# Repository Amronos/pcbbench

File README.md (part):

# PCBBench

> [!NOTE]
> PCBBench is still under development.

PCBBench compares AI models and agents on PCB design performance across 40+ metrics.

See every board, score and review at [pcbbench-five.vercel.app](https://pcbbench-five.vercel.app).

## The task

The prompt is [bench/prompt.md](bench/prompt.md).

## Results

### Complete scores

| Run                                                            | Design review (20) | Circuit checks (20) | Layout checks (30) | Orderable (20) | Parts data (10) | Failed gate | Score (100) | 5 boards, per board | AI cost |
| -------------------------------------------------------------- | ------------------ | ------------------- | ------------------ | -------------- | --------------- | ----------- | ----------- | ------------------- | ------- |
| [`sprocket--opus-5.5`][sprocket]                               | 9                  | 18.2                | 24.1               | 20             | 9.9             |             | **81.2**    | $73.36              | $53.31  |
| [`sprocket--gpt-6.1-sol`][sprocket]                            | 8                  | 19.3                | 19                 | 20             | 5               |             | **71.3**    | $148.08             | $53.72  |
| [`backplane--opus-5.5`][backplane]                             | 17                 | 17.8                | 15.4               | 10             | 9.8             |             | **69.9**    | $51.57              | $56.77  |
| [`backplane--fable-5.2`][backplane]                            | 16                 | 16.5                | 14                 | 15             | 7               |             | **68.4**    | $52.68              | $49.09  |
| [`codex-desktop`][codex][`-texttocad--gpt-6.1-sol`][texttocad] | 11                 | 20                  | 16.7               | 4              | 4.7             |             | **56.4**    | $87.53              | $14.36  |
| [`backplane--gpt-6.1-sol`][backplane]                          | 9                  | 9.2                 | 14.5               | 12             | 4.8             | −20         | **29.5**    | $181.34             | $5.81   |
| [`codex-desktop--gpt-6.1-sol`][codex]                          | 7                  | 15.6                | 9.2                | 14             | 0               | −20         | **25.9**    | $77.64              | $6.41   |

The score covers the board only. Price, AI cost and time are left out of it, so they can be weighed separately. Each item earns its points times a fraction from 0 to 1:

| Group          | Item                  | Points | Fraction                                                                                                    |
| -------------- | --------------------- | ------ | ----------------------------------------------------------------------------------------------------------- |
| Design review  | Layout                | 10     | 1 minus 0.1 per minor and 0.2 per major layout finding, down to 0                                           |
|                | Routing               | 10     | the same, for routing findings                                                                              |
| Circuit checks | Decoupling            | 5      | RP2350 power pins with a capacitor within 3.2 mm                                                            |
|                | USB protection        | 5      | 0.5 for an ESD part on D+ and D-, plus 0.25 for each line with a series resistor                            |
|                | Antenna keepout       | 5      | 1 when there are keepouts and no copper is in them                                                          |
|                | Battery drain         | 5      | 1 at 5 µA or less drawn by unswitched battery dividers, falling linearly to 0 at 25 µA                      |
| Layout checks  | Thermal pads          | 10     | mean over the exposed pads of their vias over the number needed, 0 for a pad with no plane on another layer |
|                | Grounding             | 10     | USB, QSPI and microSD track length over a ground plane on the next layer                                    |
|                | Silkscreen            | 5      | texts at least 0.8 mm high                                                                                  |
|                | Board size            | 5      | 1 at the Feather RP2350's 50.8 × 22.8 mm area or less, falling linearly to 0 at 5 times that area           |
| Orderable      | Fab notes             | 5      | 1 when every fab option in the notes can be ordered from PCBWay                                             |
|                | Board                 | 5      | 1 when the board needs no rework                                                                            |
|                | BOM lines             | 10     | 1 minus 0.2 for each BOM line that needs a fix, down to 0                                                   |
| Parts data     | 3D models             | 5      | parts with a 3D model                                                                                       |
|                | Supplier part numbers | 5      | BOM lines with a valid number from at least one supplier                                                    |

A board that fails a gate loses 20 points. The gates are a missing prompt feature, a failed crystal, button or power-path check, and a fatal review finding. Two boards fail one, each from a fatal finding listed under [Design review](#design-review). The group columns leave out the penalty. `bench/score.ts` computes the score and writes it under `score` in `metrics.json`. Differences under about 5 points aren't meaningful. Moving 10 points between any two groups moves runs by up to 2 places, and `sprocket--opus-5.5` stays first every time. `backplane--opus-5.5` and `backplane--fable-5.2`, 1.5 points apart, swap places in most shifts.

### Time, cost and price

| Run                                                            | Minutes | AI cost | Tokens, incl. cache reads | Board size (mm) | 1 board | 5 boards, per board | Prices after fixes |
| -------------------------------------------------------------- | ------- | ------- | ------------------------- | --------------- | ------- | ------------------- | ------------------ |
| [`codex-desktop--gpt-6.1-sol`][codex]                          | 78.1    | $6.41   | 21.0M                     | 80 × 65         | $246.31 | $77.64              | yes                |
| [`codex-desktop`][codex][`-texttocad--gpt-6.1-sol`][texttocad] | 96.0    | $14.36  | 52.4M                     | 80 × 75         | $297.32 | $87.53              | yes                |
| [`backplane--opus-5.5`][backplane]                             | 170.5   | $56.77  | 124.9M                    | 80 × 38         | $185.16 | $51.57              | yes                |
| [`backplane--gpt-6.1-sol`][backplane]                          | 98.2    | $5.81   | 28.6M                     | 85 × 70         | $741.00 | $181.34             | yes                |
| [`backplane--fable-5.2`][backplane]                            | 225.4   | $49.09  | 55.6M                     | 76.2 × 22.86    | $187.53 | $52.68              | yes                |
| [`sprocket--opus-5.5`][sprocket]                               | 291.0   | $53.31  | 90.1M                     | 28 × 78.54      | $282.37 | $73.36              | no                 |
| [`sprocket--gpt-6.1-sol`][sprocket]                            | 95.8    | $53.72  | 185.1M                    | 85 × 65         | $659.08 | $148.08             | no                 |

- **Minutes:** the time the agent was working.
- **AI cost:** the run's API cost at market prices, including subagents.
- **Board price:** PCB, assembly and parts, at PCBWay's normal instant-quote prices, without shipping or the new-customer $29 promo. PCBWay makes at least 5 bare PCBs, so "1 board" means 5 PCBs with 1 assembled. "5 boards" is 5 PCBs, all assembled. Parts are priced at distributor list prices for the larger of the quantity needed and the minimum order.
- **Prices after fixes:** The design couldn't be ordered exactly as delivered, so the price covers the changes listed under `fixes` in `metrics.json`. Examples are invalid or legacy part numbers, or a fab option PCBWay doesn't offer.

### BOM and 3D models

| Run                                                            | Missing 3D models | BOM lines | BOM lines fixed | Valid LCSC part numbers | Valid Digi-Key part numbers | Mouser part numbers |
| -------------------------------------------------------------- | ----------------- | --------- | --------------- | ----------------------- | --------------------------- | ------------------- |
| [`codex-desktop--gpt-6.1-sol`][codex]                          | 121               | 51        | 1               | 0%                      | 0%                          | 0%                  |
| [`codex-desktop`][codex][`-texttocad--gpt-6.1-sol`][texttocad] | 7                 | 53        | 2               | 0%                      | 0%                          | 0%                  |
| [`backplane--opus-5.5`][backplane]                             | 4                 | 38        | 0               | 100%                    | 0%                          | 0%                  |
| [`backplane--gpt-6.1-sol`][backplane]                          | 5                 | 54        | 1               | 0%                      | 0%                          | 0%                  |
| [`backplane--fable-5.2`][backplane]                            | 7                 | 36        | 0               | 50%                     | 0%                          | 0%                  |
| [`sprocket--opus-5.5`][sprocket]                               | 1                 | 40        | 0               | 100%                    | 0%                          | 0%                  |
| [`sprocket--gpt-6.1-sol`][sprocket]                            | 0                 | 55        | 0               | 0%                      | 0%                          | 0%                  |

- **Parts:** footprints on the board that aren't marked board-only, excluded from the BOM or DNP, and aren't bare test pads.
- **Missing 3D models:** parts with no 3D model, or with one that the run's own KiCad version can't load from its stock libraries and the project's files.
- **Supplier part numbers:** the share of BOM lines that give a valid part number for that supplier. An LCSC number is valid when LCSC lists it under the line's manufacturer part number. A Digi-Key number is valid when Digi-Key lists it as a variation of that part. Mouser numbers can't be looked up, so any Mouser number counts. `suppliers` in `metrics.json` has the counts.
- Every BOM covers every part. No BOM listed a designator that isn't on the board, had a Qty that doesn't match its designators, or left out a manufacturer part number for a fitted part.
- `backplane--fable-5.2` excludes its pin headers from the BOM and `sprocket--opus-5.5` marks its pin headers do not populate, so PCBWay wouldn't fit them. They aren't counted as parts. The judge sees this.

### Design and fab checks

| Run                                                            | DRC errors | DRC warnings | ERC errors | ERC warnings | BOM lines LCSC, JLCPCB or Digi-Key stocks for 5 boards | Lines discontinued at LCSC or Digi-Key |
| -------------------------------------------------------------- | ---------- | ------------ | ---------- | ------------ | ------------------------------------------------------ | -------------------------------------- |
| [`codex-desktop--gpt-6.1-sol`][codex]                          | 0          | 0            | 0          | 0            | 94.1%                                                  | 3                                      |
| [`codex-desktop`][codex][`-texttocad--gpt-6.1-sol`][texttocad] | 0          | 0            | 0          | 0            | 98.1%                                                  | 6                                      |
| [`backplane--opus-5.5`][backplane]                             | 3          | 0            | 0          | 0            | 100%                                                   | 0                                      |
| [`backplane--gpt-6.1-sol`][backplane]                          | 0          | 2            | 0          | 0            | 92.6%                                                  | 5                                      |
| [`backplane--fable-5.2`][backplane]                            | 0          | 1            | 0          | 0            | 100%                                                   | 0                                      |
| [`sprocket--opus-5.5`][sprocket]                               | 0          | 0            | 0          | 0            | 100%                                                   | 1                                      |
| [`sprocket--gpt-6.1-sol`][sprocket]                            | 0          | 0            | 0          | 0            | 100%                                                   | 7                                      |

- **DRC:** run with zones refilled, because some boards were saved with stale fills. It includes the schematic parity check. No board had unconnected items or parity issues. Copper narrower than the board's minimum connection width (`connection_width`) counts as an error, though KiCad only warns. The only cases are on `backplane--opus-5.5`, where inner-layer copper necks down to 0.079 mm, below the 5 mil (0.127 mm) minimum its PCBWay quote orders. Footprints that differ from their library copy (`lib_footprint_mismatch`) aren't counted. `metrics.json` has the counts by type.
- **Stock:** a line counts as stocked when LCSC, JLCPCB or Digi-Key has its quantity × 5 on hand, because PCBWay buys from many distributors. JLCPCB is searched by LCSC number when the line has one, else by manufacturer part number. Digi-Key is searched by manufacturer part number, including packaging variants such as `/TR`. Every run's stock was checked on the same day.
- **Discontinued:** LCSC lists the part as discontinued, or every Digi-Key listing of it is Obsolete or Discontinued at Digi-Key. Some of these parts are still in stock.
- **Fab files:** every Gerber and drill file in the order zip matches a fresh export from the board, layer by layer, within 0.1% of the drawn area. Every zip has all copper layers, Edge.Cuts, both masks, F.Silkscreen, paste for each side with surface-mount parts, and the drill files.
- **Placement:** every placement file lists every surface-mount part once, on the right side and at the board's rotation. After lining up the file's origin and axes with the board, every part is within 0.5 mm of its board position.
- **Footprints:** each part's pad count matches LCSC's footprint for its part number. Connectors aren't compared, because libraries split shield tabs and doubled contacts differently.
- **Prompt features:** every BOM has a part for the RP2350, QSPI flash, PSRAM, USB-C, Wi-Fi and BLE, microSD, Qwiic, an RGB LED and a power-path charger. Every board monitors the battery, with a fuel gauge or a resistor from a battery net to an ADC pin, directly or through a transistor.
- **Deliverables:** every run has a README, a schematic and project file next to the board, and a fab folder.
- The files checked are `board`, `bom`, `placement` and `fabZip` in `info.json`. `metrics.json` lists the designators and per-layer results.

### Circuit checks

| Run                                                            | RP2350 power pins with a capacitor within 3.2 mm | Pins farther away (mm)                                                                    | Battery divider                     | Divider current at 4.2 V (µA) | Divider switched | Antenna keepouts    | Copper in the keepouts |
| -------------------------------------------------------------- | ------------------------------------------------ | ----------------------------------------------------------------------------------------- | ----------------------------------- | ----------------------------- | ---------------- | ------------------- | ---------------------- |
| [`codex-desktop--gpt-6.1-sol`][codex]                          | 13 of 14                                         | QSPI_IOVDD 54: 3.43                                                                       | R25 100k / R26 100k, buffered by U8 | 21                            | no               | U9 footprint        | none                   |
| [`codex-desktop`][codex][`-texttocad--gpt-6.1-sol`][texttocad] | 14 of 14                                         | none                                                                                      | R10 470k / R11 470k, buffered by U9 | 4.47                          | no               | U6 footprint        | none                   |
| [`backplane--opus-5.5`][backplane]                             | 14 of 14                                         | none                                                                                      | R9 200k / R10 100k                  | 14                            | no               | U7 footprint, board | none                   |
| [`backplane--gpt-6.1-sol`][backplane]                          | 9 of 14                                          | DVDD 6: 3.45, IOVDD 11: 3.66, DVDD 23: 3.59, DVDD 39: 6.4, ADC_AVDD 44: 12.15             | R25 100k / R26 100k                 | 21                            | no               | U8 footprint, board | /3V3 fill on In4.Cu    |
| [`backplane--fable-5.2`][backplane]                            | 8 of 14                                          | IOVDD 1: 3.34, DVDD 6: 7.34, IOVDD 11: 3.69, IOVDD 20: 4.27, DVDD 23: 6.05, DVDD 39: 4.08 | R12 200k / R13 200k                 | 10.5                          | no               | board               | none                   |
| [`sprocket--opus-5.5`][sprocket]                               | 9 of 14                                          | DVDD 6: 4.53, IOVDD 11: 4.53, IOVDD 20: 7.05, DVDD 23: 6.17, IOVDD 30: 6.43               | R14 470k / R15 470k                 | 4.47                          | no               | U7 footprint        | none                   |
| [`sprocket--gpt-6.1-sol`][sprocket]                            | 12 of 14                                         | DVDD 6: 3.3, IOVDD 11: 3.3                                                                | R23 100k / R24 100k                 | 21                            | yes              | U6 footprint        | none                   |

| Run                                                            | D+ length (mm) | D- length (mm) | Mismatch (mm) | Vias | Width (mm) | Gap (mm) | Side by side (mm) | Differential impedance (Ω) | ESD parts on D+ and D- |
| -------------------------------------------------------------- | -------------- | -------------- | ------------- | ---- | ---------- | -------- | ----------------- | -------------------------- | ---------------------- |
| [`codex-desktop--gpt-6.1-sol`][codex]                          | 51.45          | 52.84          | 1.39          | 2    | 0.15       | 0.15     | 37.66             | 87.9                       | U5                     |
| [`codex-desktop`][codex][`-texttocad--gpt-6.1-sol`][texttocad] | 28.51          | 24.53          | 3.98          | 4    | 0.15       | 0.15     | 8.29              | 95.5                       | U8                     |
| [`backplane--opus-5.5`][backplane]                             | 38.02          | 38.29          | 0.27          | 0    | 0.25       | 1.25     | 11.78             | 120.9                      | U1                     |
| [`backplane--gpt-6.1-sol`][backplane]                          | 58.54          | 42.65          | 15.89         | 6    | 0.22       | 1.68     | 9.93              | no stackup                 | U5                     |
| [`backplane--fable-5.2`][backplane]                            | 44.52          | 42.26          | 2.26          | 3    | 0.15       | 0.16     | 4.86              | 114.7                      | U6                     |
| [`sprocket--opus-5.5`][sprocket]                               | 66.19          | 50.77          | 15.42         | 0    | 0.2        | 0.15     | 32.9              | 100.3                      | U4                     |
| [`sprocket--gpt-6.1-sol`][sprocket]                            | 23.84          | 25.79          | 1.95          | 2    | 0.22       | 0.15     | 8.76              | 90.7                       | D1                     |

- **Decoupling:** for each RP2350 IOVDD, DVDD, QSPI_IOVDD, USB_OTP_VDD, ADC_AVDD, VREG_VIN and VREG_AVDD pad, the nearest capacitor with one pad on that pin's net and the other on a ground net, on either side of the board. The distance is from the center of the pin's pad to the center of the capacitor's nearest pad. Pins are found by the pads' pin functions, or by RP2350A pad numbers when the footprint names none. Hardware design with RP2350 asks for decoupling close to the power pins without giving a distance. Its own Minimal board, whose capacitors it calls slightly further from the chip than optimal, has one within 3.2 mm of every power pin.
- **Battery divider:** the resistor from the battery to the ADC input, or to the op-amp follower that drives it, and the resistor from there to ground. The current is 4.2 V over their sum, from the footprint values. A divider is switched when its top resistor reaches the battery through a transistor or load switch rather than directly.
- **USB:** D+ and D- run from the RP2350 pins through the series resistors to the USB-C connector. Lengths add every track segment and arc on those nets, including stubs. Width and gap are for the longest stretch where D+ and D- segments run parallel on one layer within 2 mm of each other, and "side by side" is that stretch's length. The impedance uses the IPC-2141 edge-coupled microstrip formula with that width and gap and the board's stackup. `backplane--gpt-6.1-sol` has no stackup in its board file.
- **ESD parts:** parts other than the connector and the RP2350 with pads on both D+ and D-.
- **USB impedance isn't scored.** The RP2350 only does USB full speed. Its edges take 4 ns or more, so traces a few centimeters long behave as plain wires, and 90 Ω matching doesn't change how the link works. The same goes for how close the series resistors sit to the RP2350, which is why USB protection only checks that the ESD part and resistors are there.
- **Battery drain:** a LiPo board draws this current all the time, even when off, unless the divider is switched. `sprocket--gpt-6.1-sol` switches its divider with Q1, so it scores full points. The op-amp followers on `codex-desktop--gpt-6.1-sol` and `codex-desktop-texttocad--gpt-6.1-sol` aren't counted.
- **Antenna keepouts:** rule areas in the Wi-Fi module's footprint or on the board that overlap the module's courtyard and forbid copper. Copper in them counts tracks, vias, zone fills and other parts' pads on every copper layer, including layers the rule area doesn't cover. The rule area in the `backplane--fable-5.2` module footprint lies off the board, so only its board rule area counts.
- `design` in `metrics.json` has the per-pin distances, resistor values, net names and keepout layers.

### Layout checks

| Run                                                            | Exposed pad vias, of those needed | Thermal points | Grounded USB / QSPI / microSD | Grounding points | Texts at least 0.8 mm | Silkscreen points | Board area (mm²) | Board size points |
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
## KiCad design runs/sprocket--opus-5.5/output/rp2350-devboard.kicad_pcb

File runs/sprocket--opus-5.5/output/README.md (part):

# RP2350 dev board

A 28 × 78.54 mm, 4-layer RP2350A board with Wi-Fi/BLE, a LiPo charger and microSD, laid out for PCBWay's
standard PCB and turnkey assembly service. Every fitted part is on the top side.

| Block | Part | Notes |
| --- | --- | --- |
| MCU | RP2350A (U1), 12 MHz crystal | Core supply from the internal switching regulator (L1 3.3 µH) |
| Flash | W25Q128JVSIQ (U2), 16 MB | QSPI CS0, boots from it |
| PSRAM | APS6404L-3SQR-SN (U3), 8 MB | QSPI CS1 on GPIO8 |
| USB | USB-C (J1, GCT USB4105), 5.1 kΩ CC pull-downs, USBLC6-2 ESD | USB 2.0 full speed, power and data |
| Charger | BQ24074 (U5) with power path | 445 mA charge current, 500 mA input limit |
| Battery | JST PH 2-pin (J2), reverse-polarity P-FET (Q1) | Single-cell LiPo |
| Battery monitor | 470 k/470 k divider on GPIO28 (ADC2), switched by Q2 | `VBAT = 2 × ADC` |
| 3.3 V | TPS63001 buck-boost (U6) | Runs from the cell or USB; 3V3_EN on the header turns it off |
| Wireless | Raspberry Pi RM2 module (U7, CYW43439) | Wi-Fi 4 and Bluetooth 5.2, same wiring as the Pico 2 W |
| microSD | Molex 104031-0811 (J3) | 4-bit SD on GPIO10-15, card detect on GPIO9 |
| Qwiic / STEMMA QT | JST SH 4-pin (J4) | I²C0 on GPIO4 (SDA) and GPIO5 (SCL), 2.2 kΩ pull-ups |
| RGB LED | WS2812B-2020 (D3) | Data on GPIO22 |
| Buttons | BOOTSEL (SW1), RESET (SW2) | |
| Headers | 2 × 14 pins on 2.54 mm, rows 22.86 mm apart (J5, J6) | Holes only; not fitted. Pin names on the bottom silkscreen |

## Files

| Path | Contents |
| --- | --- |
| `rp2350-devboard.kicad_pro` | KiCad project: schematic (5 sheets) and PCB |
| `BOM.csv` | Bill of materials |
| `fab/` | Gerbers, drill files and job file (`gerbers/`, zipped as `rp2350-devboard-gerbers.zip`), PCBWay BOM and centroid |
| `docs/assembly.md` | Assembly and bring-up instructions |
| `docs/renders/` | 3D renders |
| `lib/` | Project symbols, footprints and 3D models |
| `scripts/` | Generators: `design.py` holds every part and net, the other scripts build the schematic and board, finish it (`teardrops.py`, `label_board.py`) and export `fab/` (`export_fab.py`) |

The schematic, placement and pre-routed copper come from the scripts. Edit the schematic and board in KiCad now.
`build_schematic.py` assigns new UUIDs, which breaks the link to the routed board, and `build_pcb.py` replaces the
routed board.

## Pinout

Left header J5, pin 1 at the top (USB-C is at the bottom):

| Pin | 1 | 2 | 3 | 4 | 5 | 6 | 7 | 8 | 9 | 10 | 11 | 12 | 13 | 14 |
| --- | --- | --- | --- | --- | --- | --- | --- | --- | --- | --- | --- | --- | --- | --- |
| J5 | GND | 3V3 | SWCLK | SWDIO | RUN | GP16 | GP17 | GP18 | GP19 | GP20 | GP21 | GP26/A0 | GP27/A1 | GND |
| J6 | GND | VBUS | GND | 3V3 | GP7 | GP6 | GP5/SCL | GP4/SDA | GP3 | GP2 | GP1 | GP0 | GND | 3V3_EN |

Fixed functions:

| GPIO | Function |
| --- | --- |
| 8 | PSRAM CS |
| 9 | microSD card detect (low when a card is in) |
| 10-15 | microSD CLK, CMD, D0, D1, D2, D3 |
| 22 | WS2812B data |
| 23, 24, 25, 29 | RM2 WL_ON, WL_D, WL_CS, WL_CLK (as on the Pico 2 W) |
| 28 | Battery voltage / 2 |

## Design decisions

- **Pico 2 W compatible wireless.** The RM2 uses GPIO23/24/25/29 and the same 470 Ω/10 kΩ data network, and its
  WL_GPIO2 senses VBUS through a 100 k/150 k divider. Stock MicroPython and the Pico SDK `pico2_w` board files
  drive Wi-Fi and BLE unchanged.
- **No WL_GPIO0 LED.** The Pico 2 W's LED hangs off the RM2. Its track would block the left header fan-out, and the
  RGB LED already serves as the user LED, so U7 pin 8 is unconnected. `Pin("LED")` on stock `pico2_w` firmware
  runs without error but lights nothing. Use the WS2812B on GPIO22.
- **Charger in USB500 mode.** EN1 is tied high and EN2 low, so the BQ24074 draws at most 500 mA from any USB port
  without negotiation. ISET = 2 kΩ sets 445 mA fast charge, which suits cells from about 450 mAh up. R10 (ILIM) only
  matters if EN1/EN2 are changed to resistor-programmed mode.
- **Power path.** The BQ24074 OUT pin (VSYS) feeds the TPS63001 from USB when present, else from the cell. The
  buck-boost keeps 3.3 V across the full LiPo range (3.0-4.2 V) and from USB (VSYS = 4.4 V).
- **VSYS not on the header.** VSYS is tied to the cell through the charger's internal BAT-OUT FET, so 5 V fed there
  would charge the cell with no regulation. External 5 V power goes in through VBUS (J6 pin 2), which passes the
  charger's input current limit and over-voltage protection.
- **3V3_EN.** Pulled up to VSYS with 100 kΩ. Grounding J6 pin 14 turns off 3.3 V while the charger keeps working.
- **Battery monitor back-power blocker.** The divider reads VBAT/2, up to 2.1 V. With the 3.3 V rail off, that
  voltage would forward-bias the GPIO28 clamp diode into an unpowered IOVDD. Q2, an N-FET gated by +3V3, connects
  the divider to the pin only while 3.3 V is up. The divider draws 4.5 µA from the cell.
- **2.2 kΩ PSRAM CS pull-up.** At power-on the RP2350 pulls GPIO8 down (36 kΩ minimum). 2.2 kΩ keeps CE# above
  the PSRAM's V_IH so it stays deselected until firmware configures CS1.
- **Reverse-battery P-FET (Q1).** A reversed cell leaves the FET off, so the charger and buck-boost see no
  negative voltage.
- **Headers not fitted.** J5/J6 are holes only, so the board can be soldered down, socketed or fitted with headers
  by the user. J1's four shell tabs are the only plated through-holes that get solder. PCBWay solders them with
  paste-in-hole or by hand.

## Layout

- Stackup: PCBWay standard 1.6 mm 4-layer, 1 oz outer copper, ENIG. F.Cu signals and parts, In1.Cu solid GND
  with no tracks, In2.Cu +3.3 V plane that also carries signals (see the reviewer notes), B.Cu signals with GND
  pour.
- Rules: 0.15 mm track and clearance for signals (PCBWay minimum 0.127 mm), 0.6/0.3 mm vias, USB pair 0.2 mm.
- Power copper: VBUS, VSYS, VBAT, BAT_CONN and the inductor nets run at 0.4 mm and +1V1 at 0.2-0.25 mm. The
  narrowest pieces are 0.15 mm stubs where they enter fine-pitch pins: about 0.7 mm of VBAT at U5's BAT pins and
  the EN1 tie to VSYS. +3V3 reaches the parts through the In2 plane.
- The RM2 sits at the top edge with its antenna past the copper. Its footprint carries the datasheet's RF keepout on
  all copper layers. The datasheet forbids metal only in the antenna keepout, so tracks and vias run under the module
  body.
- The RP2350 regulator follows Raspberry Pi's hardware design guide: VREG_LX runs between the C12 and C13 pads to
  L1. A custom DRC rule allows that one net 0.127 mm clearance, still at PCBWay's minimum.
- Switch-node keepouts on In2.Cu and B.Cu keep signal tracks out of the fields under the buck-boost (tracks and
  vias) and the RP2350 regulator (tracks only, so a GND via can drop the C12/C13 return straight to the plane).
  GND still pours in both.
- Drawn by hand in `scripts/hand_routes.py` and `scripts/build_pcb.py`: the top-left fan-out (SWD, RUN, GP16-27,
  VBAT_SENSE, RGB_DIN and the RM2 lines), USB_D±_MCU from U1 to R3/R4, the VREG_LX loop, and the buck-boost
  BB_L1/BB_L2/VSYS/+3V3 loop. The USB pair was routed as a differential pair and locked before the autoroute.
  The router did the rest, then GND stitching vias and a 3 mm edge fence went in.
- Teardrops on every pad and via. Reference designators are hidden on the silkscreen and shown on F.Fab.

## Reviewer notes

- **DRC.** ERC is clean. DRC has 0 errors, 0 unconnected items and clean schematic parity. One warning remains:
  R7's top silk line touched U3's pin-1 mark and was deleted, so R7 no longer matches its library footprint.
- **Via in pad.** The router put 82 vias in or against SMD pads, such as on the decoupling caps, U1, U2, U3 and J1.
  They are marked filled and capped, so the order needs PCBWay's resin-filled, capped vias, which cost more. Moving
  them beside the pads by hand would allow plain tented vias.
- **In2 is a split plane.** About 410 mm of other nets run on In2.Cu: SD bus, RUN, GP4, QSPI_SCLK (23 mm),
  PSRAM_CS, +1V1, VBUS and others. The +3.3 V copper still connects everywhere, but these traces reference a
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
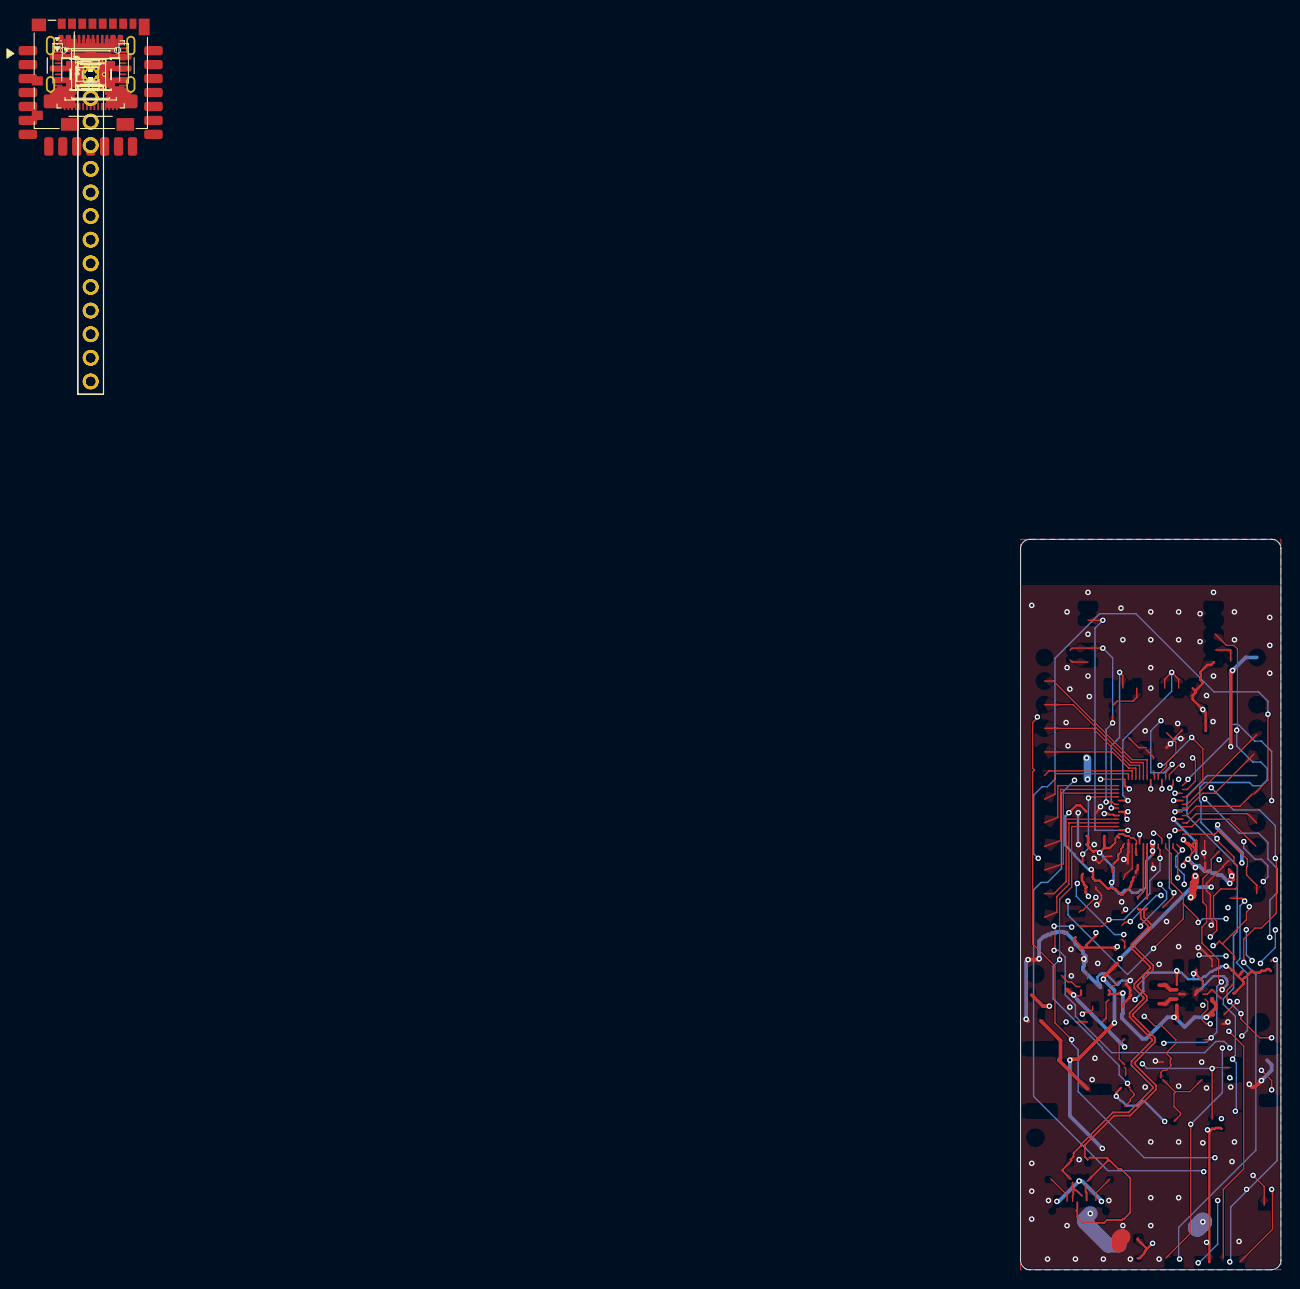
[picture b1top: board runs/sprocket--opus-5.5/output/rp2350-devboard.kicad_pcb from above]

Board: 4 copper layers, 28.0 x 78.5 mm, 87 parts (0 on the bottom side), 72 nets.

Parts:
C1, C2, C3, C4, C5, C6, C7, C8, C9, C10, C11, C17, C18, C22, C24, C28, C29, C31, C32: 100 nF; C_0402_1005Metric
C12, C13, C14: 4.7 µF; C_0402_1005Metric
C15, C16: 15 pF; C_0402_1005Metric
C19: 4.7 µF/25 V; C_0805_2012Metric
C20, C21, C23, C27, C30: 10 µF; C_0603_1608Metric
C25, C26: 22 µF; C_0805_2012Metric
D1: LED orange; LED_0603_1608Metric
D3: WS2812B-2020; LED_WS2812B-2020_PLCC4_2.0x2.0mm
FID1, FID2, FID3: Fiducial; Fiducial_1mm_Mask2mm
J1: USB-C; USB_C_Receptacle_GCT_USB4105-xx-A_16P_TopMnt_Horizontal
J2: LiPo; JST_PH_S2B-PH-SM4-TB_1x02-1MP_P2.00mm_Horizontal
J3: microSD; microSD_HC_Molex_104031-0811
J4: Qwiic; JST_SH_SM04B-SRSS-TB_1x04-1MP_P1.00mm_Horizontal
J5, J6: Header 1x14 (not fitted); PinHeader_1x14_P2.54mm_Vertical
L1: 3.3 µH; L_Abracon_AOTA-B201610S3R3-101-T
L2: 2.2 µH; L_Murata_DFE252012F
Q1: DMG2305UX; SOT-23-3
Q2: DMG1012T; SOT-523
R1: 33 Ω; R_0402_1005Metric
R2, R5, R13: 1 kΩ; R_0402_1005Metric
R3, R4: 27 Ω; R_0402_1005Metric
R6, R12, R20, R24, R25, R26, R27, R28: 10 kΩ; R_0402_1005Metric
R7, R30, R31: 2.2 kΩ; R_0402_1005Metric
R8, R9: 5.1 kΩ; R_0402_1005Metric
R10: 1.74 kΩ; R_0402_1005Metric
R11: 2 kΩ; R_0402_1005Metric
R14, R15: 470 kΩ; R_0402_1005Metric
R16: 100 Ω; R_0402_1005Metric
R17, R18, R22, R29: 100 kΩ; R_0402_1005Metric
R19: 470 Ω; R_0402_1005Metric
R23: 150 kΩ; R_0402_1005Metric
SW1: BOOTSEL; SW_SPST_PTS810
SW2: RESET; SW_SPST_PTS810
U1: RP2350A; QFN-60-1EP_7x7mm_P0.4mm_EP3.4x3.4mm_ThermalVias
U2: W25Q128JVSIQ; SOIC-8_5.3x5.3mm_P1.27mm
U3: APS6404L-3SQR-SN; SOIC-8_3.9x4.9mm_P1.27mm
U4: USBLC6-2SC6; SOT-23-6
U5: BQ24074RGTR; VQFN-16-1EP_3x3mm_P0.5mm_EP1.68x1.68mm_ThermalVias
U6: TPS63001DRCR; Texas_DRC0010J_ThermalVias
U7: RM2; RMC20452T
Y1: 12 MHz; Crystal_SMD_3225-4Pin_3.2x2.5mm

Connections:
3V3_EN: J6.14, R17.2, U6.6 (EN)
+1V1: C7.1, C8.1, C9.1, C13.1, L1.1, U1.6 (DVDD), U1.23 (DVDD), U1.39 (DVDD), U1.50 (VREG_FB)
+3V3: C1.1, C2.1, C3.1, C4.1, C5.1, C6.1, C10.1, C11.1, C12.1, C17.1, C18.1, C25.1, C26.1, C27.1, C28.1, C29.1, C30.1, C31.1, C32.1, D3.4 (VDD), J3.4 (VDD), J4.2, J5.2, J6.4, Q2.1 (G), R1.1, R6.1, R7.1, R24.1, R25.1, R26.1, R27.1, R28.1, R29.1, R30.1, R31.1, U1.1 (IOVDD), U1.11 (IOVDD), U1.20 (IOVDD), U1.30 (IOVDD), U1.38 (IOVDD), U1.44 (ADC_AVDD), U1.45 (IOVDD), U1.49 (VREG_VIN), U1.53 (USB_OTP_VDD), U1.54 (QSPI_IOVDD), U2.8 (VCC), U3.8 (VDD), U6.1 (VOUT), U6.10 (FB), U7.14 (VDDIO), U7.16 (VIN)
/MCU/BOOTSEL_SW: R5.2, SW1.1
/MCU/USB_DM_MCU: R4.1, U1.51 (USB_DM)
/MCU/USB_DP_MCU: R3.1, U1.52 (USB_DP)
/MCU/VREG_AVDD: C14.1, R1.2, U1.46 (VREG_AVDD)
/MCU/VREG_LX: L1.2, U1.48 (VREG_LX)
/MCU/XIN: C15.1, U1.21 (XIN), Y1.1
/MCU/XOUT: R2.1, U1.22 (XOUT)
/MCU/XOUT_X: C16.1, R2.2, Y1.3
/USB & Power/BAT_CONN: J2.2, Q1.3 (D)
/USB & Power/BB_L1: L2.1, U6.4 (L1)
/USB & Power/BB_L2: L2.2, U6.2 (L2)
/USB & Power/BB_VINA: C24.1, R16.2, U6.8 (VINA)
/USB & Power/CC1: J1.A5 (CC1), R8.1
/USB & Power/CC2: J1.B5 (CC2), R9.1
/USB & Power/CHG_ILIM: R10.1, U5.12 (ILIM)
/USB & Power/CHG_ISET: R11.1, U5.16 (ISET)
/USB & Power/CHG_LED: D1.2 (A), R13.2
/USB & Power/CHG_N: D1.1 (K), U5.9 (~CHG)
/USB & Power/CHG_TS: R12.1, U5.1 (TS)
/USB & Power/VBAT_DIV: Q2.3 (D), R14.2, R15.1
/Wireless/WL_D_470R: R19.2, U7.6 (SPI_DO)
/Wireless/WL_IRQ: R20.2, U7.10 (~IRQ)
/Wireless/WL_VBUS_DET: R22.2, R23.1, U7.17 (GPIO2)
GND: C1.2, C2.2, C3.2, C4.2, C5.2, C6.2, C7.2, C8.2, C9.2, C10.2, C11.2, C12.2, C13.2, C14.2, C15.2, C16.2, C17.2, C18.2, C19.2, C20.2, C21.2, C22.2, C23.2, C24.2, C25.2, C26.2, C27.2, C28.2, C29.2, C30.2, C31.2, C32.2, D3.2 (VSS), J1.A1 (GND), J1.A12 (GND), J1.B1 (GND), J1.B12 (GND), J1.SH (SHIELD), J2.1, J3.6 (VSS), J3.10 (DET_A), J3.SH (SHIELD), J4.1, J5.1, J5.14, J6.1, J6.3, J6.13, Q1.1 (G), R8.2, R9.2, R10.2, R11.2, R12.2, R15.2, R18.2, R23.2, SW1.2, SW2.2, U1.47 (VREG_PGND), U1.61 (GND), U2.4 (GND), U3.4 (VSS), U4.2 (GND), U5.4 (~CE), U5.5 (EN2), U5.8 (VSS), U5.17 (VSS), U6.3 (PGND), U6.9 (GND), U6.11 (PGND), U7.1 (GND), U7.4 (GND), U7.7 (GND), U7.11 (GND), U7.15 (GND), U7.21 (GND), Y1.2 (G), Y1.4 (G)
GP0: J6.12, U1.2 (GPIO0)
GP1: J6.11, U1.3 (GPIO1)
GP2: J6.10, U1.4 (GPIO2)
GP3: J6.9, U1.5 (GPIO3)
GP4_SDA: J4.3, J6.8, R30.2, U1.7 (GPIO4)
GP5_SCL: J4.4, J6.7, R31.2, U1.8 (GPIO5)
GP6: J6.6, U1.9 (GPIO6)
GP7: J6.5, U1.10 (GPIO7)
GP16: J5.6, U1.27 (GPIO16)
GP17: J5.7, U1.28 (GPIO17)
GP18: J5.8, U1.29 (GPIO18)
GP19: J5.9, U1.31 (GPIO19)
GP20: J5.10, U1.32 (GPIO20)
GP21: J5.11, U1.33 (GPIO21)
GP26_A0: J5.12, U1.40 (GPIO26/ADC0)
GP27_A1: J5.13, U1.41 (GPIO27/ADC1)
PSRAM_CS: R7.2, U1.12 (GPIO8), U3.1 (~CE)
PS_SYNC: R18.1, U6.7 (PS/SYNC), U7.18 (GPIO1)
QSPI_SCLK: U1.56 (QSPI_SCLK), U2.6 (CLK), U3.6 (SCLK)
QSPI_SD0: U1.57 (QSPI_SD0), U2.5 (DI/IO_{0}), U3.5 (SI/SIO0)
QSPI_SD1: U1.59 (QSPI_SD1), U2.2 (DO/IO_{1}), U3.2 (SO/SIO1)
QSPI_SD2: U1.58 (QSPI_SD2), U2.3 (~WP/IO_{2}), U3.3 (SIO2)
QSPI_SD3: U1.55 (QSPI_SD3), U2.7 (~HOLD/~RESET/IO_{3}), U3.7 (SIO3)
QSPI_SS: R5.1, U1.60 (~QSPI_SS), U2.1 (~CS)
RGB_DIN: D3.3 (DIN), U1.34 (GPIO22)
RUN: J5.5, R6.2, SW2.1, U1.26 (RUN)
SD_CLK: J3.5 (CLK), U1.14 (GPIO10)
SD_CMD: J3.3 (CMD), R24.2, U1.15 (GPIO11)
SD_D0: J3.7 (DAT0), R25.2, U1.16 (GPIO12)
SD_D1: J3.8 (DAT1), R26.2, U1.17 (GPIO13)
SD_D2: J3.1 (DAT2), R27.2, U1.18 (GPIO14)
SD_D3: J3.2 (DAT3/CD), R28.2, U1.19 (GPIO15)
SD_DET: J3.9 (DET_B), R29.2, U1.13 (GPIO9)
SWCLK: J5.3, U1.24 (SWCLK)
SWDIO: J5.4, U1.25 (SWDIO)
USB_DM: J1.A7 (D-), J1.B7 (D-), R4.2, U4.3 (I/O2), U4.4 (I/O2)
USB_DP: J1.A6 (D+), J1.B6 (D+), R3.2, U4.1 (I/O1), U4.6 (I/O1)
VBAT: C21.1, Q1.2 (S), R14.1, U5.2 (BAT), U5.3 (BAT)
VBAT_SENSE: C22.1, Q2.2 (S), U1.42 (GPIO28/ADC2)
VBUS: C19.1, J1.A4 (VBUS), J1.A9 (VBUS), J1.B4 (VBUS), J1.B9 (VBUS), J6.2, R22.1, U4.5 (VBUS), U5.13 (IN)
VSYS: C20.1, C23.1, R13.1, R16.1, R17.1, U5.6 (EN1), U5.10 (OUT), U5.11 (OUT), U6.5 (VIN)
WL_CLK: U1.43 (GPIO29/ADC3), U7.3 (SPI_CLK)
WL_CS: U1.37 (GPIO25), U7.9 (SPI_CS)
WL_D: R19.1, R20.1, U1.36 (GPIO24), U7.5 (SPI_DI)
WL_ON: U1.35 (GPIO23), U7.12 (WL_ON), U7.13 (BT_ON)

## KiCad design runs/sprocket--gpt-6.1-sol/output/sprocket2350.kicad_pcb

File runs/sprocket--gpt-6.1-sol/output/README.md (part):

# Sprocket 2350

RP2350A development board with 16 MiB QSPI flash, 8 MiB PSRAM, USB-C device interface, rechargeable single-cell battery power, ESP32-C3 Wi-Fi/BLE, SPI microSD, Qwiic/STEMMA QT and an addressable RGB indicator.

## Release status

Prototype design. No hardware has been built or tested. The revised layout uses the Raspberry Pi regulator core, a compact charger/buck-boost stage, local radio bypassing and a shorter USB route. The files in `fab/` support PCBWay's prototype quote and engineering review. They do not establish bench performance or manufacturer acceptance.

Before ordering, PCBWay must confirm exact sourcing, controlled impedance, filled/capped vias and complete assembly. Qualify the built prototype before production release. See [release-review.md](fab/release-review.md).

## Design choices

| Item | Choice |
|---|---|
| MCU | Bare RP2350A, current stepping to be confirmed by supplier |
| Memory | W25Q128JVSIQ flash; APS6404L-3SQR-SN PSRAM on shared QSPI bus with GPIO0 CS1 |
| Radio | ESP32-C3-WROOM-02-N4, integrated antenna beyond the PCB edge |
| Power | BQ24074 power-path charger, approximately 303 mA charge setting; TPS63001 fixed 3.3 V buck-boost |
| Battery | External protected 1S 4.2 V LiPo pack, cell-mounted 10 kΩ B3435 NTC, keyed 3-pin JST PH |
| PCB | 85 × 65 mm, four copper layers, top-side components and two factory-installed through-hole headers |
| Debug | RP2350 SWD header; RP BOOTSEL/reset and ESP boot/reset buttons |
| RGB | WS2812C-2020-V6, manufacturer-supported 3.3 V operation, not an older WS2812 substitution |

PCBWay must source and install every BOM reference, including headers J5/J6. No part is reserved for user assembly.

## Interfaces and firmware

| Function | RP2350 GPIO |
|---|---|
| PSRAM CS | 0, QMI CS1n |
| Qwiic SDA / SCL | 2 / 3, I²C1 |
| ESP RX / TX | RP TX 4 → ESP RX20; RP RX 5 ← ESP TX21, UART1 |
| microSD MISO / CS / CLK / MOSI | 8 / 9 / 10 / 11, SPI1 |
| RGB data | 20, PIO |
| ESP EN / BOOT | 23 / 24. Drive EN high to enable; drive BOOT low/release for download mode. |
| USB input limit | 6. Low/high impedance selects USB100; high selects USB500. J5 pin 4 is unused. |
| Card detect | 25, low when inserted |
| Battery monitor | 26 / ADC0, VBAT = 2 × measured ADC voltage |

Initialize PSRAM through QMI. Observe the manufacturer's startup/reset, refresh and maximum chip-select duration limits. Begin with conservative QSPI and SD clock rates. The ESP module needs application firmware or a compatible ESP-AT build. RP firmware can bridge the UART to program the ESP while controlling its boot/reset pins. No firmware image is included or tested.

Hold RP BOOTSEL while releasing RESET to enter the USB ROM loader. BOOTSEL alone does not reset the MCU. SWD reference voltage is an output, not a board power input.

### Expansion header J5

Numbering follows the square pin-1 pad on the assembly drawing. All signals are 3.3 V.

| Odd pin | Signal | Even pin | Signal |
|---:|---|---:|---|
| 1 | 3V3 output | 2 | GND |
| 3 | GP1 | 4 | Unused |
| 5 | GP7 | 6 | GP15 |
| 7 | GP16 | 8 | GP17 |
| 9 | GP18 | 10 | GP19 |
| 11 | GP12 | 12 | GP13 |
| 13 | GP14 | 14 | GP22 |
| 15 | CHG, active low | 16 | GP21 |
| 17 | GP27 / ADC1 | 18 | GP28 / ADC2 |
| 19 | GP29 / ADC3 | 20 | GND |

J6 pins 1–4 are 3V3 reference output, SWDIO, SWCLK and GND. J4 pins 1–4 are GND, 3V3 output, SDA and SCL.

## Power and safety limits

- USB is a 5 V sink/device, not USB PD and not a host. Separate 5.1 kΩ CC resistors are fitted.
- Startup selects USB100 and holds the ESP disabled. Firmware may drive GP6 high only after the source permits 500 mA. Keep GP23 low until the supply budget allows radio operation. Do not enable the radio, SD writes or external Qwiic loads on a 100 mA budget.
- This prototype does not guarantee generic legacy-host pre-enumeration or suspend compliance. SD, RGB and Qwiic power are not hardware-gated, and the ROM loader does not implement this board's power policy. Use a source explicitly allowing 500 mA for USB-only development, or a protected battery with a qualified USB host. Do not advertise USB certification.
- The 500 mA USB budget includes both system load and charging. The charger reduces charging and can supplement from the battery. Wi-Fi transmission, SD writes and Qwiic loads must be qualified together. Do not assume USB-only operation supports every combined peak.
- Use a protected 4.2 V single-cell pack that permits at least 335 mA charging and the measured peak discharge current. The board charger is not pack overdischarge or short-circuit protection.
- J3 pin 1 is BAT+, pin 2 GND, pin 3 NTC. NTC must connect to GND in the pack and contact the cell. This is not a standard two-wire JST battery pinout. Check polarity before connecting.
- The direct NTC circuit allows approximately 0–50°C charging, with tolerance. Only use cells qualified for that range; cells limited to 45°C need tighter charge inhibition.
- Battery monitoring uses a PMOS switch enabled from the live 3.3 V rail through an NMOS. This avoids an always-connected battery divider when the MCU is unpowered. Its startup/shutdown transient still needs bench validation.
- Do not drive GPIO, SWD, I²C or UART from powered external equipment while the board is unpowered. Expansion pins are 3.3 V interfaces. Do not inject power through J4/J5/J6.
- WS2812C-V6's below-3.3 V behavior is not specified. Qualify indicator operation at worst-case rail tolerance and temperature. Do not substitute older 5 V-only LED revisions.

## Manufacturing files

Open `sprocket2350.kicad_pro` with KiCad 10.99 or a compatible newer release. Embedded symbols and footprints allow inspection without regeneration. Generation tools use the connector's `kicad-python`, headless API and KiCad 10 library tables.

[Fabrication package](fab/README.md), [BOM](fab/BOM.csv), [assembly instructions](fab/assembly.md) and [procurement checks](fab/procurement.md) are in `fab/`. The package includes Gerbers, drills, position CSV, schematic PDF, assembly drawings and check reports for review.

Final all-severity ERC and DRC report zero violations, zero opens and zero schematic parity issues under the project's recorded check settings. The BOM, schematic, PCB and placement file agree on all 93 fitted references. All component model files exist. The package identifies 18 vias requiring filled/capped processing.

PCBWay must confirm sourcing in its quote; distributor stock is not PCBWay inventory. No quote or order has been placed.

## Review before release

1. Review final ERC/DRC reports, confirm complete routing and accept zero opens/shorts. Review all warnings; do not dismiss physical violations as library noise.
2. Verify L2's lower-left winding dot on the assembly drawing. Check filled/capped vias and the charger/regulator paste process.
3. Have PCBWay confirm the proposed four-layer stackup and 90 Ω ±10% USB impedance. The nominal dielectric dimensions are a quote target, not a field-solver or manufacturer sign-off.
4. Verify footprints and pin 1 against ordered USB, JST, SD and QFN package drawings. RF antenna area must remain copper- and enclosure-free.
5. Confirm component sourcing, full through-hole assembly and panel rails/fiducials with PCBWay.
6. After building an accepted prototype, test USB enumeration in both plug orientations, ROM boot/SWD, flash/PSRAM stress, SD writes, Wi-Fi/BLE, RGB, Qwiic, battery ADC and all USB/battery insertion sequences. Test NTC open/short and charger current/temperature before production release.

## Sources

- [RP2350 hardware design guide](https://datasheets.raspberrypi.com/rp2350/hardware-design-with-rp2350.pdf)
- [RP2350 datasheet](https://datasheets.raspberrypi.com/rp2350/rp2350-datasheet.pdf)
- [BQ24074 datasheet](https://www.ti.com/lit/ds/symlink/bq24074.pdf)
- [TPS63001 datasheet](https://www.ti.com/lit/ds/symlink/tps63001.pdf)
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
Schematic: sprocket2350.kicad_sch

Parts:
C1, C20: 1 µF; C_0402_1005Metric_bd85cb550de6; MPN GRM155R61A105KE15D
C2, C16, C19, C33, C34: 100 nF; C_0402_1005Metric_bd85cb550de6; MPN GRM155R71C104KA88D
C3, C4: 15 pF; C_0402_1005Metric_bd85cb550de6; MPN GRM1555C1H150JA01D
C5, C32: 4.7 µF; C_0402_Reference_Wide_14cca4d2f3c2; MPN GRM155R60J475ME47D
C6, C7, C9, C10, C13, C14, C15, C29: 100 nF; C_0402_1005Metric_5bb70af72c21; MPN GRM155R71C104KA88D
C8: 4.7 µF; C_0402_1005Metric_3d5b6007ab61; MPN GRM155R60J475ME87D
C11, C12, C17: 100 nF; C_0402_1005Metric_3d5b6007ab61; MPN GRM155R71C104KA88D
C18: 1 µF; C_0402_1005Metric_3d5b6007ab61; MPN GRM155R61A105KE15D
C21, C22: 4.7 µF; C_0603_1608Metric_fc57b2d2c517; MPN GRM188R61A475KE15D
C23: 10 µF; C_0805_2012Metric_9b2498f01ab8; MPN GRM21BR61A106KE19L
C24: 10 µF; C_0805_2012Metric_2a2089b9c0e0; MPN GRM21BR61A106KE19L
C25: 100 nF; C_0402_1005Metric_379fea1f11f0; MPN GRM155R71C104KA88D
C26, C27: 22 µF; C_0805_2012Metric_9b2498f01ab8; MPN GRM21BR60J226ME39L
C28: 10 µF; C_0805_2012Metric_9aa12f2a5b38; MPN GRM21BR61A106KE19L
C30: 10 µF; C_0805_2012Metric_3c44b73798b4; MPN GRM21BR61A106KE19L
C31: 4.7 µF; C_0402_Reference_e393483276fd; MPN GRM155R60J475ME47D
D1: USB ESD; SOT-23-6_9f72e7298dc2; MPN USBLC6-2SC6
D2: RGB; LED_WS2812B-2020_PLCC4_2.0x2.0mm_a21191c056fd; MPN WS2812C-2020-V6
J1: USB-C; USB_C_Receptacle_HRO_TYPE-C-31-M-12_f41bc01c523c; MPN TYPE-C-31-M-12
J2: microSD SPI; microSD_HC_Hirose_DM3AT-SF-PEJM5_c8561cc7c035; MPN DM3AT-SF-PEJM5
J3: LiPo + NTC; JST_PH_S3B-PH-SM4-TB_1x03-1MP_P2.00mm_Horizontal_7d858e54ec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; MPN S3B-PH-SM4-TB(LF)(SN)
J4: Qwiic / STEMMA QT; JST_SH_BM04B-SRSS-TB_1x04-1MP_P1.00mm_Vertical_15770d88cefa; MPN BM04B-SRSS-TB(LF)(SN)
J5: GPIO expansion; PinHeader_2x10_P2.54mm_Vertical_6b6633ddffb1; MPN 61302021121
J6: SWD; PinHeader_1x04_P2.54mm_Vertical_aa6e1eda1045; MPN 61300411121
L1: 2.2 µH; L_Bourns-SRN4018_023b05217879; MPN SRN4018-2R2M
L2: 3.3 µH; Abracon_AOTA_B201610S_Reversed_8ee5be28bd5d; MPN AOTA-B201610S3R3-101-T
Q1: Battery sense gate; SOT-23_0f2464f3dff4; MPN BSS84,215
Q2: Sense enable; SOT-23_0f2464f3dff4; MPN 2N7002,215
R1, R2: 5.1 kΩ; R_0402_1005Metric_c12575d0a1b0; MPN RC0402FR-075K1L
R3, R4: 27 Ω; R_0402_1005Metric_47d8607f7501; MPN RC0402FR-0727RL
R5, R6, R8, R18: 10 kΩ; R_0402_1005Metric_c12575d0a1b0; MPN RC0402FR-0710KL
R7, R34: 1 kΩ; R_0402_1005Metric_012c2e6e4d3c; MPN RC0402FR-071KL
R9: 2.2 kΩ; R_0402_1005Metric_012c2e6e4d3c; MPN RC0402FR-072K2L
R10, R11, R12, R26, R27, R28, R29, R30, R31: 10 kΩ; R_0402_1005Metric_012c2e6e4d3c; MPN RC0402FR-0710KL
R13: 2.94 kΩ; R_0402_1005Metric_387807b4f148; MPN RC0402FR-072K94L
R14: 3.83 kΩ; R_0402_1005Metric_ea43ba4c9899; MPN RC0402FR-073K83L
R15: 46.4 kΩ; R_0402_1005Metric_387807b4f148; MPN RC0402FR-0746K4L
R16: 2.0 kΩ; R_0402_1005Metric_387807b4f148; MPN RC0402FR-072KL
R17: 10 kΩ; R_0402_1005Metric_8c22085481f2; MPN RC0402FR-0710KL
R19: 0 Ω; R_0402_1005Metric_012c2e6e4d3c; MPN RC0402FR-070RL
R20: 2.2 kΩ; R_0402_1005Metric_ea43ba4c9899; MPN RC0402FR-072K2L
R21, R22: 4.7 kΩ; R_0402_1005Metric_c12575d0a1b0; MPN RC0402FR-074K7L
R23, R24: 100 kΩ; R_0402_1005Metric_012c2e6e4d3c; MPN RC0402FR-07100KL
R25: 1 kΩ; R_0402_1005Metric_c12575d0a1b0; MPN RC0402FR-071KL
R32: 33 Ω; R_0402_Reference_7dfa1b5439a9; MPN RC0402FR-0733RL
R33: 330 Ω; R_0402_1005Metric_012c2e6e4d3c; MPN RC0402FR-07330RL
R35, R36: 100 kΩ; R_0402_1005Metric_c12575d0a1b0; MPN RC0402FR-07100KL
SW1: BOOT_SW; SW_SPST_B3U-1000P_0467a73a7d37; MPN B3U-1000P
SW2: RUN; SW_SPST_B3U-1000P_0467a73a7d37; MPN B3U-1000P
SW3: RADIO_BOOT; SW_SPST_B3U-1000P_0467a73a7d37; MPN B3U-1000P
SW4: RADIO_EN; SW_SPST_B3U-1000P_0467a73a7d37; MPN B3U-1000P
U1: RP2350A; QFN-60-1EP_7x7mm_P0.4mm_EP3.4x3.4mm_90ff6dc065bf; MPN RP2350A
U2: 16 MB QSPI; SOIC-8_5.3x5.3mm_P1.27mm_e11bfd68aeed; MPN W25Q128JVSIQ
U3: 8 MB PSRAM; SOIC-8_3.9x4.9mm_P1.27mm_55c97adfff38; MPN APS6404L-3SQR-SN
U4: BQ24074; VQFN-16-1EP_3x3mm_P0.5mm_EP1.6x1.6mm_6e643c636e65; MPN BQ24074RGTR
U5: 3.3 V buck-boost; Texas_DRC0010J_a64bda92039e; MPN TPS63001DRCR
U6: Wi-Fi + BLE; ESP32-C3-WROOM-02_dbcdfb5211c9; MPN ESP32-C3-WROOM-02-N4
Y1: 12 MHz; Crystal_SMD_3225-4Pin_3.2x2.5mm_3559e2579f46; MPN ABM8-272-T3

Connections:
/1V1: C5.1, C6.1, C7.1, C8.1, L2.2, U1.6 (DVDD), U1.23 (DVDD), U1.39 (DVDD), U1.50 (VREG_FB)
/3V3: C9.1, C10.1, C11.1, C12.1, C13.1, C14.1, C15.1, C16.1, C17.1, C18.1, C19.1, C20.1, C26.1, C27.1, C28.1, C29.1, C30.1, C32.1, C33.1, D2.4 (VDD), J2.4 (VDD), J4.2, J5.1, J6.1, Q2.1 (G), R5.1, R6.1, R8.1, R10.1, R11.1, R12.1, R17.1, R18.1, R21.1, R22.1, R26.1, R27.1, R28.1, R29.1, R30.1, R31.1, R32.1, R36.1, U1.1 (IOVDD), U1.11 (IOVDD), U1.20 (IOVDD), U1.30 (IOVDD), U1.38 (IOVDD), U1.44 (ADC_AVDD), U1.45 (IOVDD), U1.49 (VREG_VIN), U1.53 (USB_OTP_VDD), U1.54 (QSPI_IOVDD), U2.8 (VCC), U3.8 (VDD), U5.1 (VOUT), U5.10 (FB), U6.1 (3V3)
/BAT: C22.1, J3.1, Q1.2 (S), R35.1, U4.2 (BAT), U4.3 (BAT)
/BAT_ADC: C2.1, R23.2, R24.1, U1.40 (GPIO26/ADC0)
/BAT_GATE: Q1.1 (G), Q2.3 (D), R35.2
/BAT_NTC: J3.3, U4.1 (TS)
/BAT_SENSE: Q1.3 (D), R23.1
/BOOT_SW: R7.2, SW1.1
/CC1: J1.A5 (CC1), R1.1
/CC2: J1.B5 (CC2), R2.1
/CHG: J5.15, R17.2, U4.9 (~CHG)
/CORE_LX: L2.1, U1.48 (VREG_LX)
/FLASH_CS: R5.2, R7.1, U1.60 (~QSPI_SS), U2.1 (~CS)
/GND: C1.2, C2.2, C3.2, C4.2, C5.2, C6.2, C7.2, C8.2, C9.2, C10.2, C11.2, C12.2, C13.2, C14.2, C15.2, C16.2, C17.2, C18.2, C19.2, C20.2, C21.2, C22.2, C23.2, C24.2, C25.2, C26.2, C27.2, C28.2, C29.2, C30.2, C31.2, C32.2, C33.2, C34.2, D1.2 (GND), D2.2 (VSS), J1.A1 (GND), J1.A12 (GND), J1.B1 (GND), J1.B12 (GND), J1.SH (SHIELD), J2.6 (VSS), J2.10 (DET_A), J2.SH (SHIELD), J3.2, J4.1, J5.2, J5.20, J6.4, Q2.2 (S), R1.2, R2.2, R9.2, R13.2, R14.2, R15.2, R16.2, R20.2, R24.2, R36.2, SW1.2, SW2.2, SW3.2, SW4.2, U1.47 (VREG_PGND), U1.61 (GND), U2.4 (GND), U3.4 (VSS), U4.4 (~CE), U4.5 (EN2), U4.8 (VSS), U4.17 (VSS), U5.3 (PGND), U5.7 (PS/SYNC), U5.9 (GND), U5.11 (PGND), U6.9 (GND), U6.19 (GND), Y1.2 (G), Y1.4 (G)
/GP1: J5.3, U1.3 (GPIO1)
/GP6: R19.1, U1.9 (GPIO6)
/GP7: J5.5, U1.10 (GPIO7)
/GP12: J5.11, U1.16 (GPIO12)
/GP13: J5.12, U1.17 (GPIO13)
/GP14: J5.13, U1.18 (GPIO14)
/GP15: J5.6, U1.19 (GPIO15)
/GP16: J5.7, U1.27 (GPIO16)
/GP17: J5.8, U1.28 (GPIO17)
/GP18: J5.9, U1.29 (GPIO18)
/GP19: J5.10, U1.31 (GPIO19)
/GP21: J5.16, U1.33 (GPIO21)
/GP22: J5.14, U1.34 (GPIO22)
/GP27: J5.17, U1.41 (GPIO27/ADC1)
/GP28: J5.18, U1.42 (GPIO28/ADC2)
/GP29: J5.19, U1.43 (GPIO29/ADC3)
/ILIM: R14.1, U4.12 (ILIM)
/ISET: R13.1, U4.16 (ISET)
/ITERM: R16.1, U4.15 (ITERM)
/PGOOD: R18.2, U4.7 (~PGOOD)
/PSRAM_CS: R6.2, U1.2 (GPIO0), U3.1 (~CE)
/PWR_L1: L1.1, U5.4 (L1)
/PWR_L2: L1.2, U5.2 (L2)
/QSPI_CLK: U1.56 (QSPI_SCLK), U2.6 (CLK), U3.6 (SCLK)
/QSPI_D0: U1.57 (QSPI_SD0), U2.5 (DI/IO_{0}), U3.5 (SI/SIO0)
/QSPI_D1: U1.59 (QSPI_SD1), U2.2 (DO/IO_{1}), U3.2 (SO/SIO1)
/QSPI_D2: U1.58 (QSPI_SD2), U2.3 (~WP/IO_{2}), U3.3 (SIO2)
/QSPI_D3: U1.55 (QSPI_SD3), U2.7 (~HOLD/~RESET/IO_{3}), U3.7 (SIO3)
/RADIO_BOOT: R10.2, R34.2, SW3.1, U6.8 (IO9)
/RADIO_BOOT_DRIVE: R34.1, U1.36 (GPIO24)
/RADIO_EN: C1.1, R9.1, R33.2, SW4.1, U6.2 (EN)
/RADIO_EN_DRIVE: R33.1, U1.35 (GPIO23)
/RADIO_IO2: R12.2, U6.16 (IO2)
/RADIO_IO8: R11.2, U6.7 (IO8)
/RADIO_RX: U1.7 (GPIO4), U6.11 (IO20/RXD)
/RADIO_TX: U1.8 (GPIO5), U6.12 (IO21/TXD)
/RGB_DATA: D2.3 (DIN), U1.32 (GPIO20)
/RUN: R8.2, SW2.1, U1.26 (RUN)
/SCL: J4.4, R22.2, U1.5 (GPIO3)
/SDA: J4.3, R21.2, U1.4 (GPIO2)
/SD_CLK: J2.5 (CLK), U1.14 (GPIO10)
/SD_CS: J2.2 (DAT3/CD), R26.2, U1.13 (GPIO9)
/SD_DAT1: J2.8 (DAT1), R29.2
/SD_DAT2: J2.1 (DAT2), R30.2
/SD_DETECT: J2.9 (DET_B), R31.2, U1.37 (GPIO25)
/SD_MISO: J2.7 (DAT0), R28.2, U1.12 (GPIO8)
/SD_MOSI: J2.3 (CMD), R27.2, U1.15 (GPIO11)
/SWCLK: J6.3, U1.24 (SWCLK)
/SWDIO: J6.2, U1.25 (SWDIO)
/SYS: C23.1, C24.1, C25.1, U4.10 (OUT), U4.11 (OUT), U5.5 (VIN), U5.6 (EN), U5.8 (VINA)
/TMR: R15.1, U4.14 (TMR)
/USB_CONN_DM: D1.3 (I/O2), D1.4 (I/O2), J1.A7 (D-), J1.B7 (D-), R4.1
/USB_CONN_DP: D1.1 (I/O1), D1.6 (I/O1), J1.A6 (D+), J1.B6 (D+), R3.1
/USB_DM: R4.2, U1.51 (USB_DM)
/USB_DP: R3.2, U1.52 (USB_DP)
/USB_LIMIT: R19.2, R20.1, U4.6 (EN1)
/VBUS: C21.1, C34.1, D1.5 (VBUS), J1.A4 (VBUS), J1.A9 (VBUS), J1.B4 (VBUS), J1.B9 (VBUS), U4.13 (IN)
/VREG_AVDD: C31.1, R32.2, U1.46 (VREG_AVDD)
/XIN: C3.1, U1.21 (XIN), Y1.1
/XOUT: R25.2, U1.22 (XOUT)
/XTAL_OUT: C4.1, R25.1, Y1.3

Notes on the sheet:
USB-C / protection
Core decoupling
Battery sense
Charger / battery
GPIO / I2C / SWD / RGB
Radio
microSD
3.3 V buck-boost
MCU / core
QSPI flash / PSRAM
Power flags

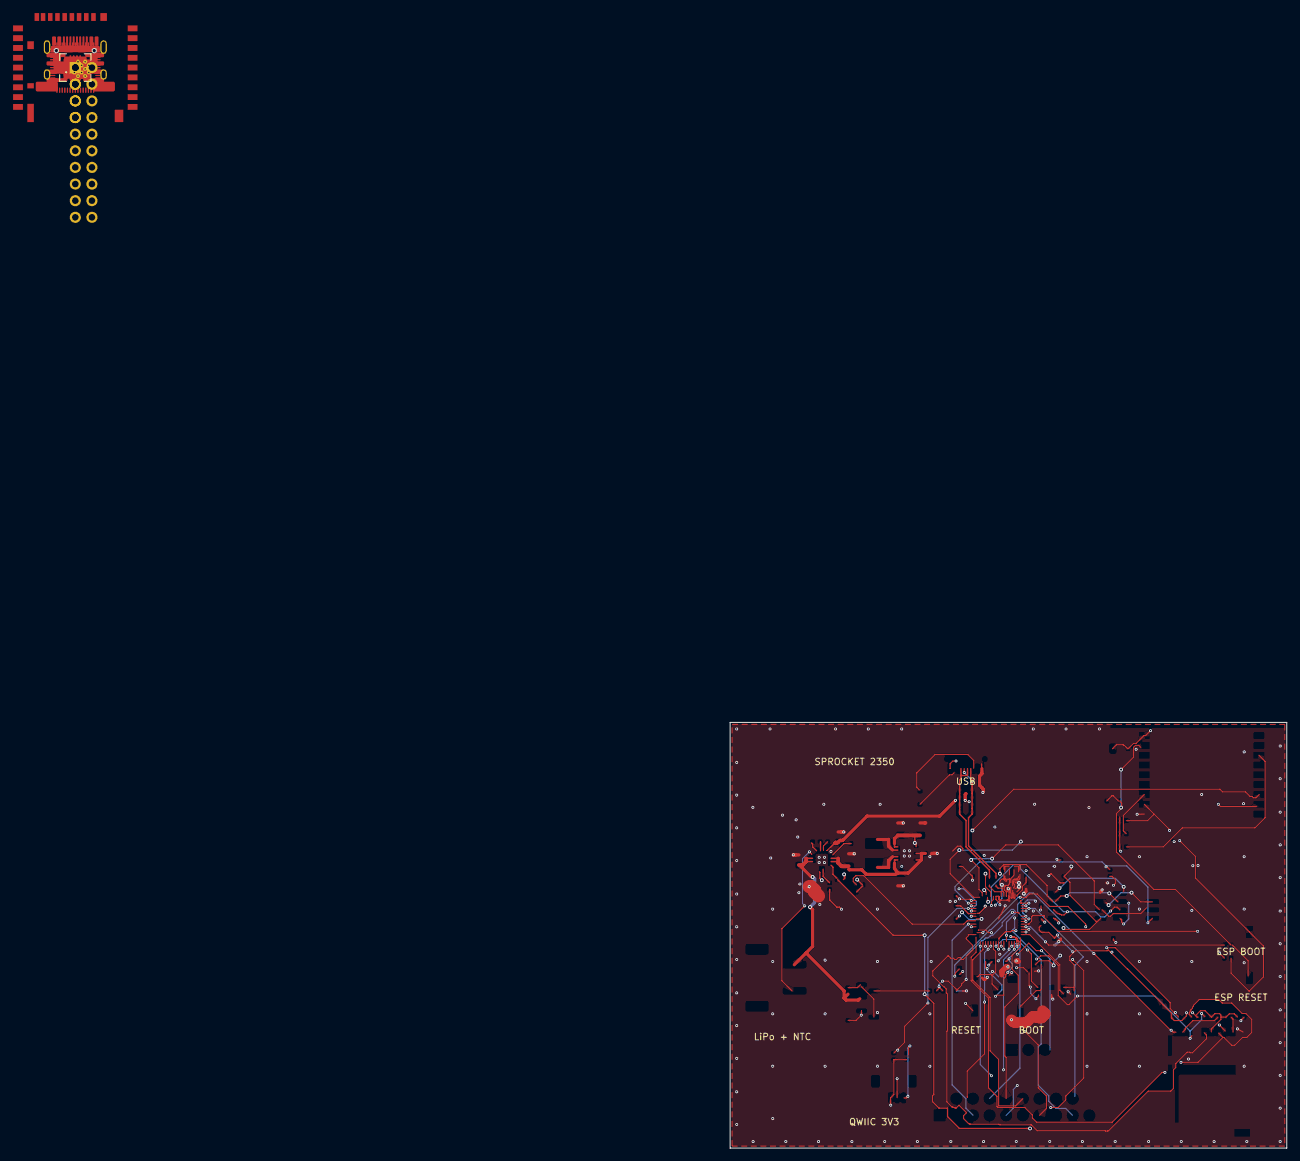
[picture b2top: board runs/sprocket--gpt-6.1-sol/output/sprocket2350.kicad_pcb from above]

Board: 4 copper layers, 85.0 x 65.0 mm, 93 parts (0 on the bottom side), 75 nets.

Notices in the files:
parts and their libraries:
From Raspberry Pi RP2350A Minimal design R4 (MIT licence), ref C14
From Raspberry Pi RP2350A Minimal design R4 (MIT licence), ref X1
From Raspberry Pi RP2350A Minimal design R4 (MIT licence), ref U3
From Raspberry Pi RP2350A Minimal design R4 (MIT licence), ref R10
